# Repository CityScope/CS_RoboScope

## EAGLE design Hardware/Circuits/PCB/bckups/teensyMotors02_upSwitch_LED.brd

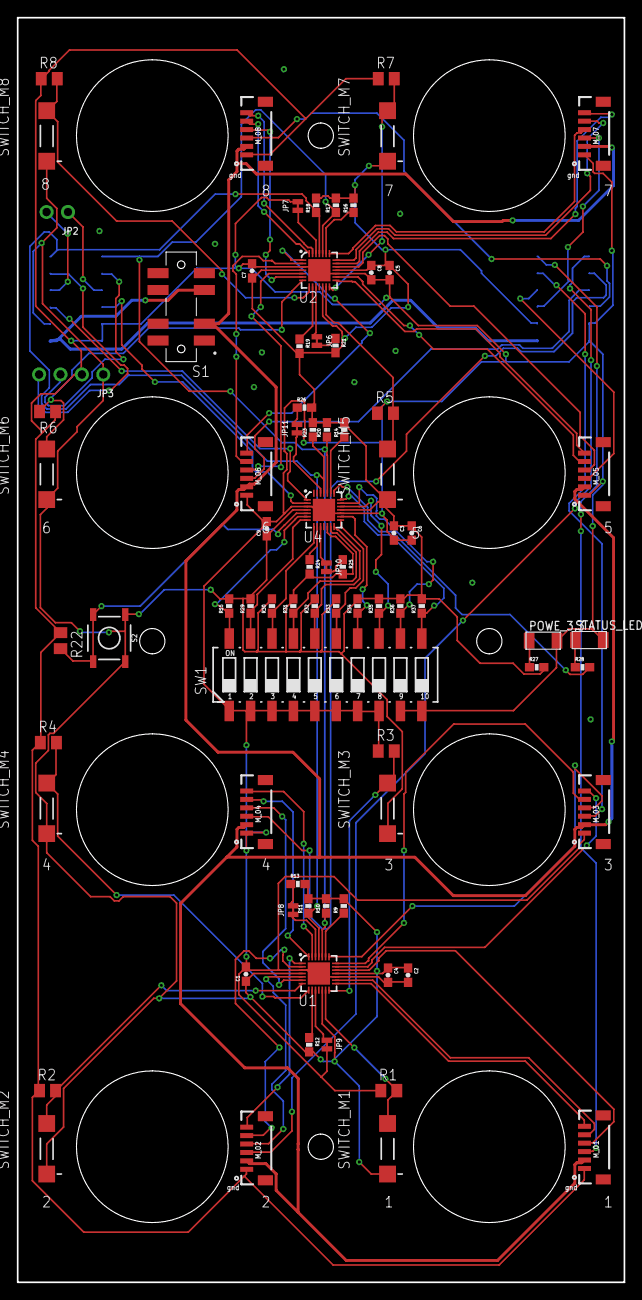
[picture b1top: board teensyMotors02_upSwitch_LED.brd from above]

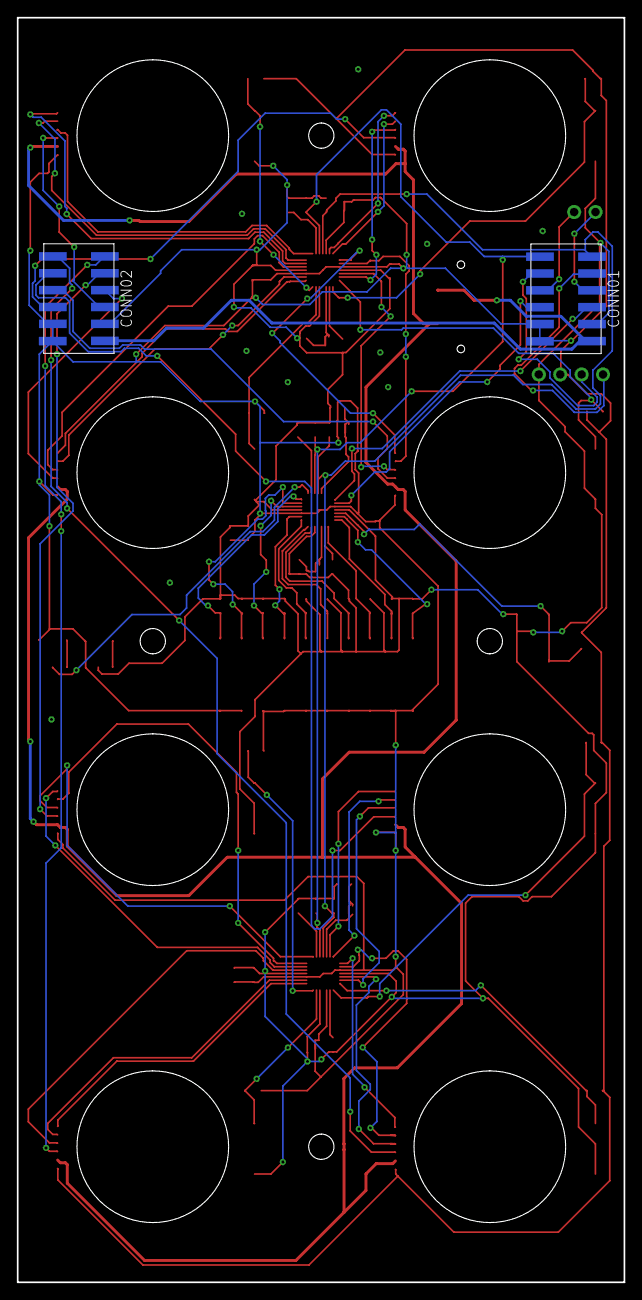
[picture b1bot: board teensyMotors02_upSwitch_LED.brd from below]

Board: 2 copper layers, 72.0 x 150.1 mm, 80 parts (2 on the bottom side), 82 nets.

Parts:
C1, C2, C3, C4, C5, C6, C7, C8, C9: 0.1uF; 0603-CAP
CONN01, CONN02: TMMH-105-12
JP2: 1X02_ROUND
JP3: 1X04_ROUND
JP6, JP7, JP8, JP9, JP10, JP11: JUMPER-SMT_2_NC_TRACE_NO-SILK; SMT-JUMPER_2_NC_TRACE_NO-SILK
M_01, M_02, M_03, M_04, M_05, M_06, M_07, M_08: 1X06-1MM
POWE_3.3: LEDFAB1206; LED1206FAB
R1, R2, R3, R5, R6, R7, R8: 10k; M0805
R4, R22: 10K; M0805
R9, R10, R11, R12, R13, R14, R15, R16, R17, R18, R19, R20, R21, R23, R24, R25, R26, R29, R30, R31, R32, R33, R34, R35, R36, R37: 10K; 0603-RES
R27, R28: 500; 0603-RES
S1: JS207011SCQNR; SW_JS207011SCQNR
S2: TACTILE_SWITCH_SMD_5.2MM
STATUS_LED: LEDFAB1206; LED1206FAB
SW1: 219-10; CTS-219-10
SWITCH_M1, SWITCH_M2, SWITCH_M3, SWITCH_M4, SWITCH_M5, SWITCH_M6, SWITCH_M7, SWITCH_M8: DTSM-3
U1, U2, U4: SX1509; QFN-28

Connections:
0_SX1: M_04.6, U1.27
0_SX2: M_08.6, U2.27
1_SX1: M_04.5, U1.28
1_SX2: M_08.5, U2.28
2_SX1: M_02.6, U1.1
2_SX2: M_06.6, U2.1
2_SX3: CONN01.8, U4.1
3.3V: C1.1, C2.1, C3.1, C4.1, C5.1, C6.1, C7.1, C8.1, C9.1, CONN01.10, CONN02.10, JP3.1, R9.2, R10.2, R11.2, R12.2, R13.2, R14.2, R15.2, R16.2, R17.2, R18.2, R19.2, R20.2, R21.2, R23.2, R24.2, R25.2, R26.2, R27.2, R29.2, R30.2, R31.2, R32.2, R33.2, R34.2, R35.2, R36.2, R37.2, S2.1, S2.2, SWITCH_M1.1, SWITCH_M2.1, SWITCH_M3.1, SWITCH_M4.1, SWITCH_M5.1, SWITCH_M6.1, SWITCH_M7.1, SWITCH_M8.1, U1.4, U1.12, U1.18, U2.4, U2.12, U2.18, U4.4, U4.12, U4.18
3_SX1: M_02.5, U1.2
3_SX2: M_06.5, U2.2
3_SX3: CONN01.7, U4.2
4_SX1: M_02.4, U1.5
4_SX2: M_06.4, U2.5
4_SX3: R22.2, S2.3, S2.4, U4.5
5_SX1: M_04.4, U1.6
5_SX2: M_08.4, U2.6
5_SX3: R15.1, SW1.20, U4.6
6_SX1: R2.2, SWITCH_M2.2, U1.7
6_SX2: R6.2, SWITCH_M6.2, U2.7
6_SX3: R29.1, SW1.19, U4.7
7_SX1: R4.2, SWITCH_M4.2, U1.8
7_SX2: R8.2, SWITCH_M8.2, U2.8
7_SX3: R30.1, SW1.18, U4.8
8_SX1: R1.2, SWITCH_M1.2, U1.13
8_SX2: R5.2, SWITCH_M5.2, U2.13
8_SX3: R31.1, SW1.17, U4.13
9_SX1: R3.2, SWITCH_M3.2, U1.14
9_SX2: R7.2, SWITCH_M7.2, U2.14
9_SX3: R32.1, SW1.16, U4.14
10_SX1: M_01.6, U1.15
10_SX2: M_05.6, U2.15
10_SX3: R33.1, SW1.15, U4.15
11_SX1: M_01.5, U1.16
11_SX2: M_05.5, U2.16
11_SX3: R34.1, SW1.14, U4.16
12_SX1: M_01.4, U1.19
12_SX2: M_05.4, U2.19
12_SX3: R35.1, SW1.13, U4.19
13_SX1: M_03.6, U1.20
13_SX2: M_07.6, U2.20
13_SX3: R36.1, SW1.12, U4.20
14_SX1: M_03.5, U1.21
14_SX2: M_07.5, U2.21
14_SX3: R37.1, SW1.11, U4.21
15_SX1: M_03.4, U1.22
15_SX2: M_07.4, U2.22
15_SX3: R28.2, U4.22
!INT_SX1: R12.1, U1.9
!INT_SX2: R19.1, U2.9
!INT_SX3: R24.1, U4.9
!RESET_SX1: R9.1, U1.23
!RESET_SX2: R16.1, U2.23
!RESET_SX3: R14.1, U4.23
ADDR0_SX1: JP8.1, U1.26
ADDR0_SX2: JP7.1, U2.26
ADDR0_SX3: JP11.1, U4.26
ADDR1_SX1: JP9.1, U1.10
ADDR1_SX2: JP6.1, U2.10
ADDR1_SX3: JP10.1, U4.10
CAN_RX2: CONN01.4, JP3.4
CAN_TX2: CONN01.3, JP3.3
GND_MCU: C1.2, C2.2, C3.2, C4.2, C5.2, C6.2, C7.2, C8.2, C9.2, CONN01.9, CONN01.11, CONN02.9, CONN02.11, JP3.2, JP7.2, JP9.2, M_01.1, M_02.1, M_03.1, M_04.1, M_05.1, M_06.1, M_07.1, M_08.1, POWE_3.3.2, R1.1, R2.1, R3.1, R4.1, R5.1, R6.1, R7.1, R8.1, R22.1, STATUS_LED.2, SW1.1, SW1.2, SW1.3, SW1.4, SW1.5, SW1.6, SW1.7, SW1.8, SW1.9, SW1.10, U1.3, U1.17, U1.29, U2.3, U2.17, U2.29, U4.3, U4.17, U4.29
unnamed: JP6.2, R21.1
unnamed: JP8.2, R13.1
unnamed: R28.1, STATUS_LED.1
unnamed: JP10.2, R25.1
unnamed: JP11.2, R26.1
unnamed: POWE_3.3.1, R27.1
NEOPIXEL_01: CONN02.2, M_01.3
NEOPIXEL_02: CONN02.1, M_02.3
NEOPIXEL_03: CONN02.4, M_03.3
NEOPIXEL_04: CONN02.3, M_04.3
NEOPIXEL_05: CONN02.6, M_05.3
NEOPIXEL_06: CONN02.5, M_06.3
NEOPIXEL_07: CONN02.8, M_07.3
NEOPIXEL_08: CONN02.7, M_08.3
RX7: CONN01.6, JP2.2
SCL_00: CONN01.2, R11.1, R18.1, R23.1, U1.25, U2.25, U4.25
SDA_00: CONN01.1, R10.1, R17.1, R20.1, U1.24, U2.24, U4.24
TX7: CONN01.5, JP2.1
VCC_5V: M_01.2, M_02.2, M_03.2, M_04.2, M_05.2, M_06.2, M_07.2, M_08.2, S1.2
VCC_5V_IN: CONN01.12, CONN02.12, S1.3

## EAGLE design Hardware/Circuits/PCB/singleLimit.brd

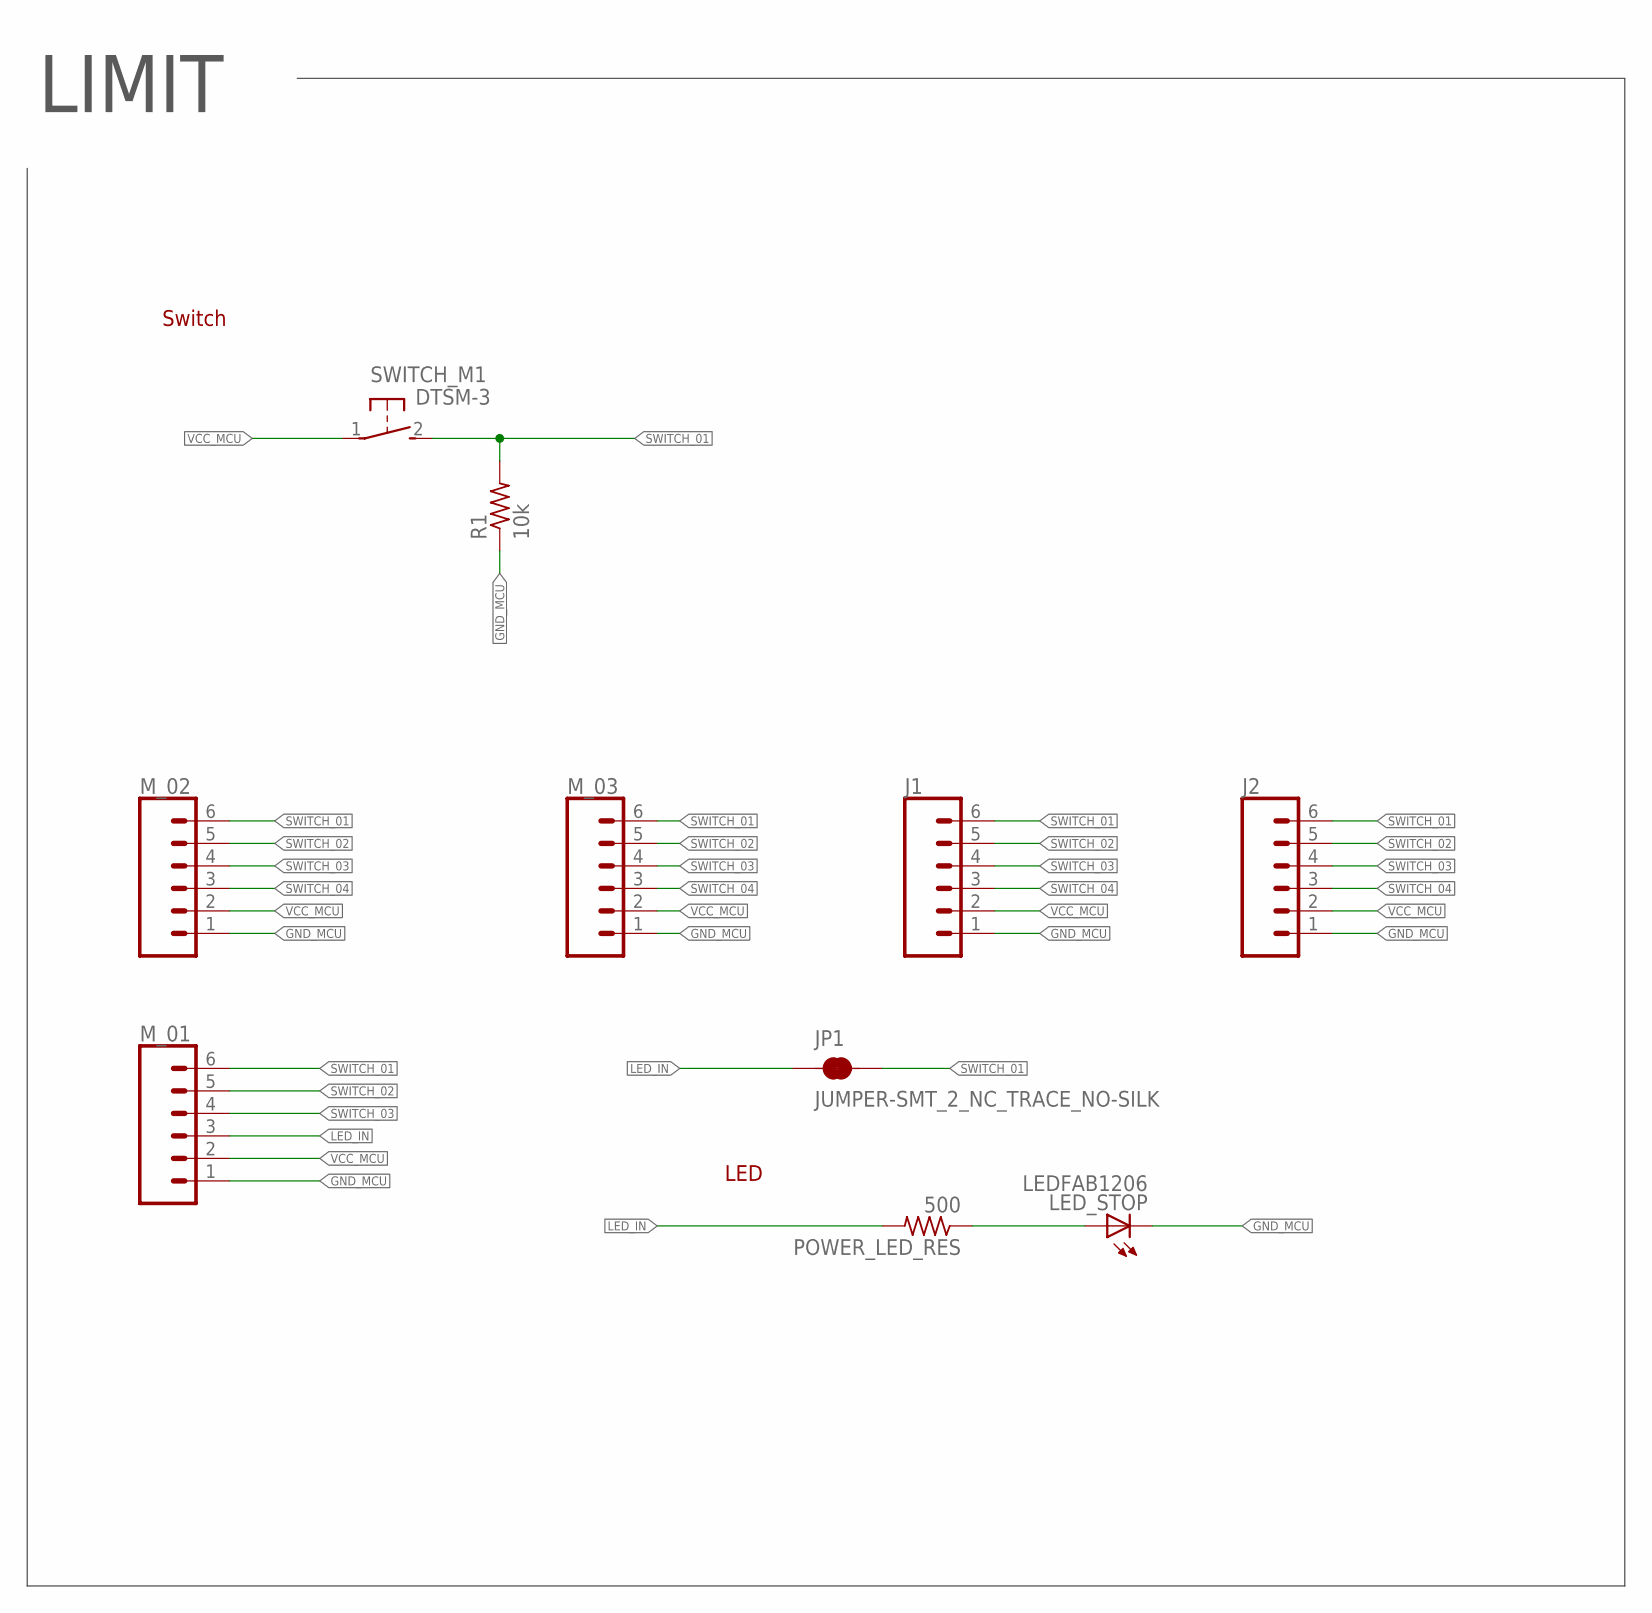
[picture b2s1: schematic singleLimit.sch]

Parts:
J1, J2: CONN_06NO_SILK_FEMALE_PTH; 1X06_NO_SILK
JP1: JUMPER-SMT_2_NC_TRACE_NO-SILK; SMT-JUMPER_2_NC_TRACE_NO-SILK
LED_STOP: LEDFAB1206; LED1206FAB
M_01, M_02, M_03: CONN_06SMD-1MM; 1X06-1MM
POWER_LED_RES: 500; M0805
R1: 10k; M0805
SWITCH_M1: DTSM-3

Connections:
GND_MCU: J1.1, J2.1, LED_STOP.2 (C), M_01.1, M_02.1, M_03.1, R1.1
LED_IN: JP1.1, M_01.3, POWER_LED_RES.2
unnamed: LED_STOP.1 (A), POWER_LED_RES.1
SWITCH_01: J1.6, J2.6, JP1.2, M_01.6, M_02.6, M_03.6, R1.2, SWITCH_M1.2
SWITCH_02: J1.5, J2.5, M_01.5, M_02.5, M_03.5
SWITCH_03: J1.4, J2.4, M_01.4, M_02.4, M_03.4
SWITCH_04: J1.3, J2.3, M_02.3, M_03.3
VCC_MCU: J1.2, J2.2, M_01.2, M_02.2, M_03.2, SWITCH_M1.1

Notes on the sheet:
LIMIT
LED
Switch

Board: 2 copper layers, 10 parts (5 on the bottom side), 8 nets, no tracks yet.

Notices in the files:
parts and their libraries:
SparkFun-Connectors: Licensing: Creative Commons ShareAlike 4.0 International - https://creativecommons.org/licenses/by-sa/4.0
SparkFun-DigitalIC: Licensing: CC v3.0 Share-Alike You are welcome to use this library for commercial purposes.
